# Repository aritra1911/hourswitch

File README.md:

# Hour Switch
A relay operated switch which can switch between powering devices, each for a duration of 4 hours.

## Input
9 to 20 V DC, 1 A.

## TODO
- [ ] Make switching hours programmable via DIP switches.

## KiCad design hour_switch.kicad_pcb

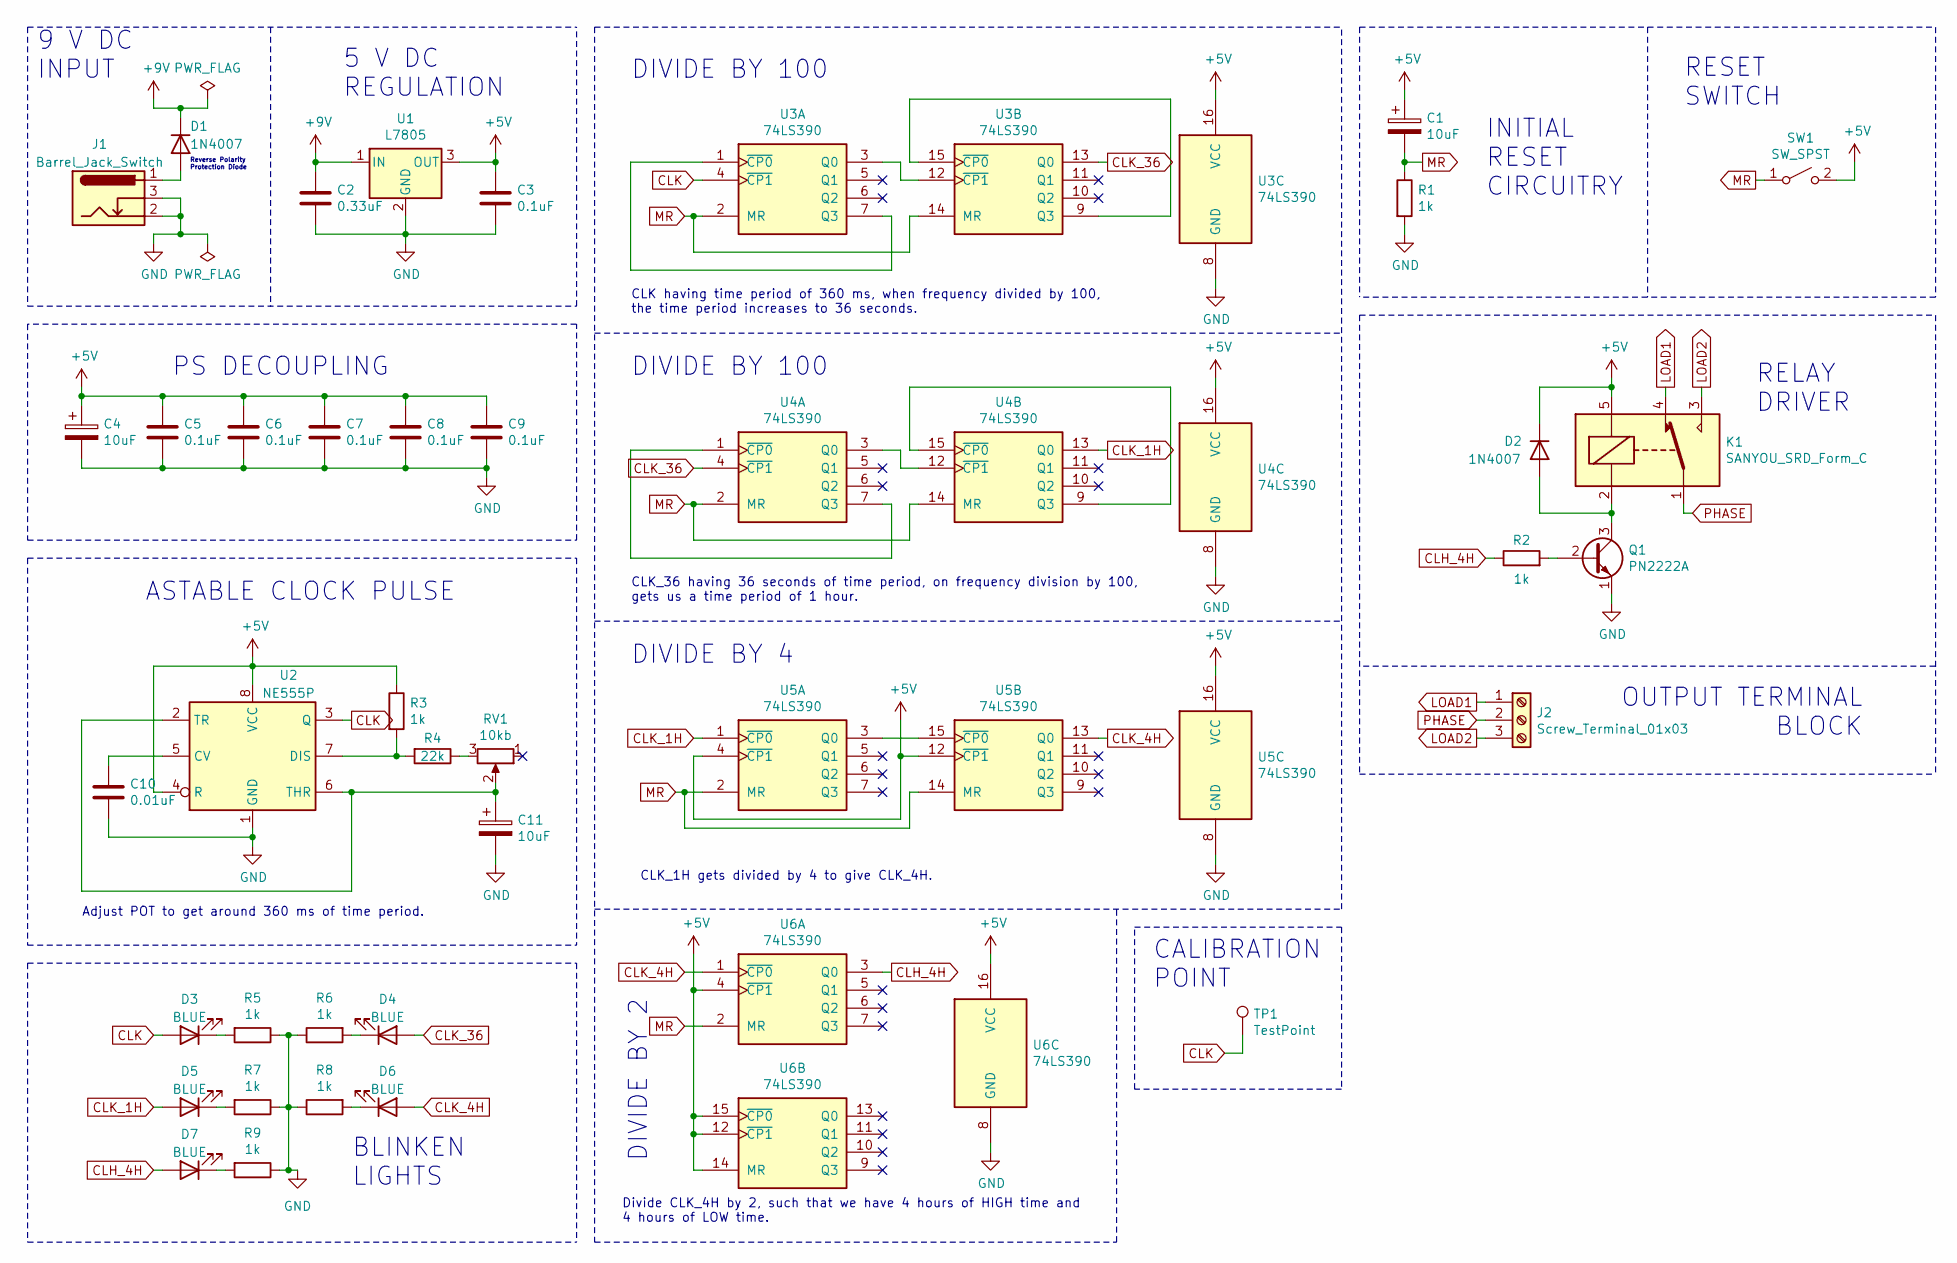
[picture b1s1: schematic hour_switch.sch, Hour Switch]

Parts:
C1, C4, C11: 10uF; CP_Radial_D5.0mm_P2.00mm
C2: 0.33uF; C_Rect_L24.0mm_W7.0mm_P22.50mm_MKT
C3, C5, C6, C7, C8, C9: 0.1uF; C_1206_3216Metric
C10: 0.01uF; C_Disc_D3.0mm_W2.0mm_P2.50mm
D1, D2: 1N4007; D_5W_P10.16mm_Horizontal
D3, D4, D5, D6, D7: BLUE; LED_1206_3216Metric
J1: Barrel_Jack_Switch; BarrelJack_Horizontal
J2: Screw_Terminal_01x03; TerminalBlock_Altech_AK300-3_P5.00mm
K1: SANYOU_SRD_Form_C; Relay_SPDT_SANYOU_SRD_Series_Form_C
Q1: PN2222A; TO-92_Inline_Wide
R1, R2, R3, R5, R6, R7, R8, R9: 1k; R_1206_3216Metric
R4: 22k; R_Axial_DIN0207_L6.3mm_D2.5mm_P10.16mm_Horizontal
RV1: 10kb; Potentiometer_Bourns_3386P_Vertical
SW1: SW_SPST; SW_PUSH_6mm_H4.3mm
TP1: TestPoint; TestPoint_Bridge_Pitch2.54mm_Drill1.0mm
U1: L7805; TO-220-3_Horizontal_TabDown_NoDrill
U2: NE555P; DIP-8_W7.62mm_Socket_LongPads
U3, U4, U5, U6: 74LS390; DIP-16_W7.62mm_Socket_LongPads

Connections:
+5V: C1.1, C3.1, C4.1, C5.1, C6.1, C7.1, C8.1, C9.1, D2.1 (K), K1.5, R3.1, SW1.2 (B), U1.3 (OUT), U2.4 (R), U2.8 (VCC), U3.16 (VCC), U4.16 (VCC), U5.4 (~CP1), U5.12 (~CP1), U5.16 (VCC), U6.4 (~CP1), U6.12 (~CP1), U6.14 (MR), U6.15 (~CP0), U6.16 (VCC)
+9V: C2.1, D1.1 (K), U1.1 (IN)
CLH_4H: D7.2 (A), R2.1, U6.3 (Q0)
CLK: D3.2 (A), TP1.1, U2.3 (Q), U3.4 (~CP1)
CLK_1H: D5.2 (A), U4.13 (Q0), U5.1 (~CP0)
CLK_4H: D6.2 (A), U5.13 (Q0), U6.1 (~CP0)
CLK_36: D4.2 (A), U3.13 (Q0), U4.4 (~CP1)
GND: C2.2, C3.2, C4.2, C5.2, C6.2, C7.2, C8.2, C9.2, C10.2, C11.2, J1.2, J1.3, Q1.1 (E), R1.2, R5.1, R6.1, R7.1, R8.1, R9.1, U1.2 (GND), U2.1 (GND), U3.8 (GND), U4.8 (GND), U5.8 (GND), U6.8 (GND)
LOAD1: J2.1, K1.4
LOAD2: J2.3, K1.3
MR: C1.2, R1.1, SW1.1 (A), U3.2 (MR), U3.14 (MR), U4.2 (MR), U4.14 (MR), U5.2 (MR), U5.14 (MR), U6.2 (MR)
unnamed: C10.1, U2.5 (CV)
unnamed: C11.1, RV1.2, U2.2 (TR), U2.6 (THR)
unnamed: D1.2 (A), J1.1
unnamed: D2.2 (A), K1.2, Q1.3 (C)
unnamed: D3.1 (K), R5.2
unnamed: D4.1 (K), R6.2
unnamed: D5.1 (K), R7.2
unnamed: D6.1 (K), R8.2
unnamed: D7.1 (K), R9.2
unnamed: Q1.2 (B), R2.2
unnamed: R3.2, R4.2, U2.7 (DIS)
unnamed: R4.1, RV1.3
unnamed: U3.1 (~CP0), U3.7 (Q3)
unnamed: U3.3 (Q0), U3.12 (~CP1)
unnamed: U3.9 (Q3), U3.15 (~CP0)
unnamed: U4.1 (~CP0), U4.7 (Q3)
unnamed: U4.3 (Q0), U4.12 (~CP1)
unnamed: U4.9 (Q3), U4.15 (~CP0)
unnamed: U5.3 (Q0), U5.15 (~CP0)
PHASE: J2.2, K1.1

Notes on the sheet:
DIVIDE BY 2
RELAY DRIVER
DIVIDE BY 100
DIVIDE BY 4
ASTABLE CLOCK PULSE
Adjust POT to get around 360 ms of time period.
PS DECOUPLING
INITIAL RESET CIRCUITRY
5 V DC REGULATION
9 V DC INPUT
OUTPUT TERMINAL BLOCK
BLINKEN LIGHTS
CLK having time period of 360 ms, when frequency divided by 100, the time period increases to 36 seconds.
CLK_36 having 36 seconds of time period, on frequency division by 100, gets us a time period of 1 hour.
RESET SWITCH
CALIBRATION POINT
Reverse Polarity Protection Diode
CLK_1H gets divided by 4 to give CLK_4H.
Divide CLK_4H by 2, such that we have 4 hours of HIGH time and 4 hours of LOW time.

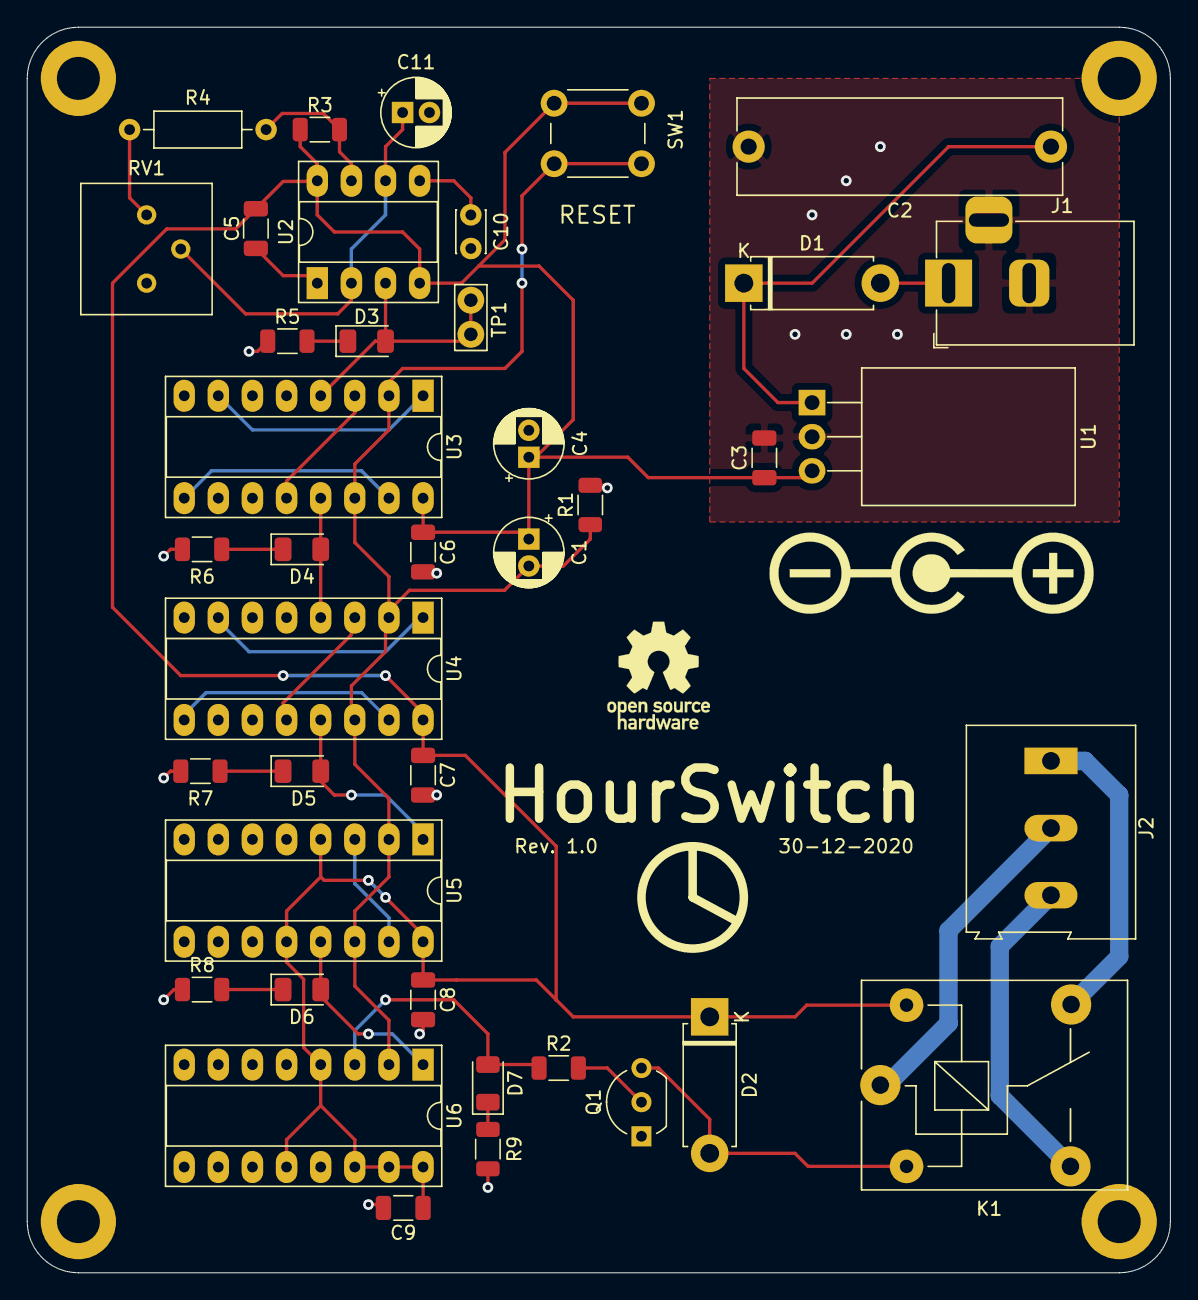
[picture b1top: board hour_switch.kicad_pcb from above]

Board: 2 copper layers, 85.1 x 92.7 mm, 40 parts (0 on the bottom side), 31 nets.

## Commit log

2020-12-30 Rev. 1.0
